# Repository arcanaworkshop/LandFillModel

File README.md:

# README Landfill Model Guide

Create by George Spearing for Arcana Workshop
March 2020

## Purpose

The lanfill model is run by an Arduino Nano with a breakout board to control audio track files. The audio track files live on the microSD card in the breakout board. Formmating for files are shown below.

## Audio Track Naming

The audio tracks are labeled using the scheme "TRACK000.wav" where "000" is the track identifier. These track numbers correspond to the buttons which light up specific sections.

## Track Numbering

- "000" Electric Power Plant
- "001" Empty - Not Used
- "002" Ground Water
- "003" Ground Liner
- "004" Leache Runoff
- "005" Gas Collection
- "006" Garbage Layer
- "007" Ground (Surface Layer)

## Track Formatting

The Arduino uses the TMRpcm library to play audio track from a microSD card. The full documentation for this library can be found at [https://github.com/TMRh20/TMRpcm/wiki](https://github.com/TMRh20/TMRpcm/wiki).

In summary, the tracks should be formatted as follows:

- Mono track
- 32000Hz (22050, 1600, 11025 also work)
- WAV, Unsigned 8 bit PCM

## Programming

I hope this doesn't need to be reprogrammed. There are two nano boards. 1 is the master and mainly controls all the leds. This is also the master to control the slave arduino file playing. The salve nano is a dedicated audio interpreter and player. This uses the micro SD card breakout. To program the slave nano, the SD car must NOT be connected. the MISO/MISI connections with the usbtiny during programming fail the upload. There is a switch on the circuit board that disables the SD card interface. Turn this off when progrmaming. DON'T FORGET TO TURN BACK ON ONCE DONE.

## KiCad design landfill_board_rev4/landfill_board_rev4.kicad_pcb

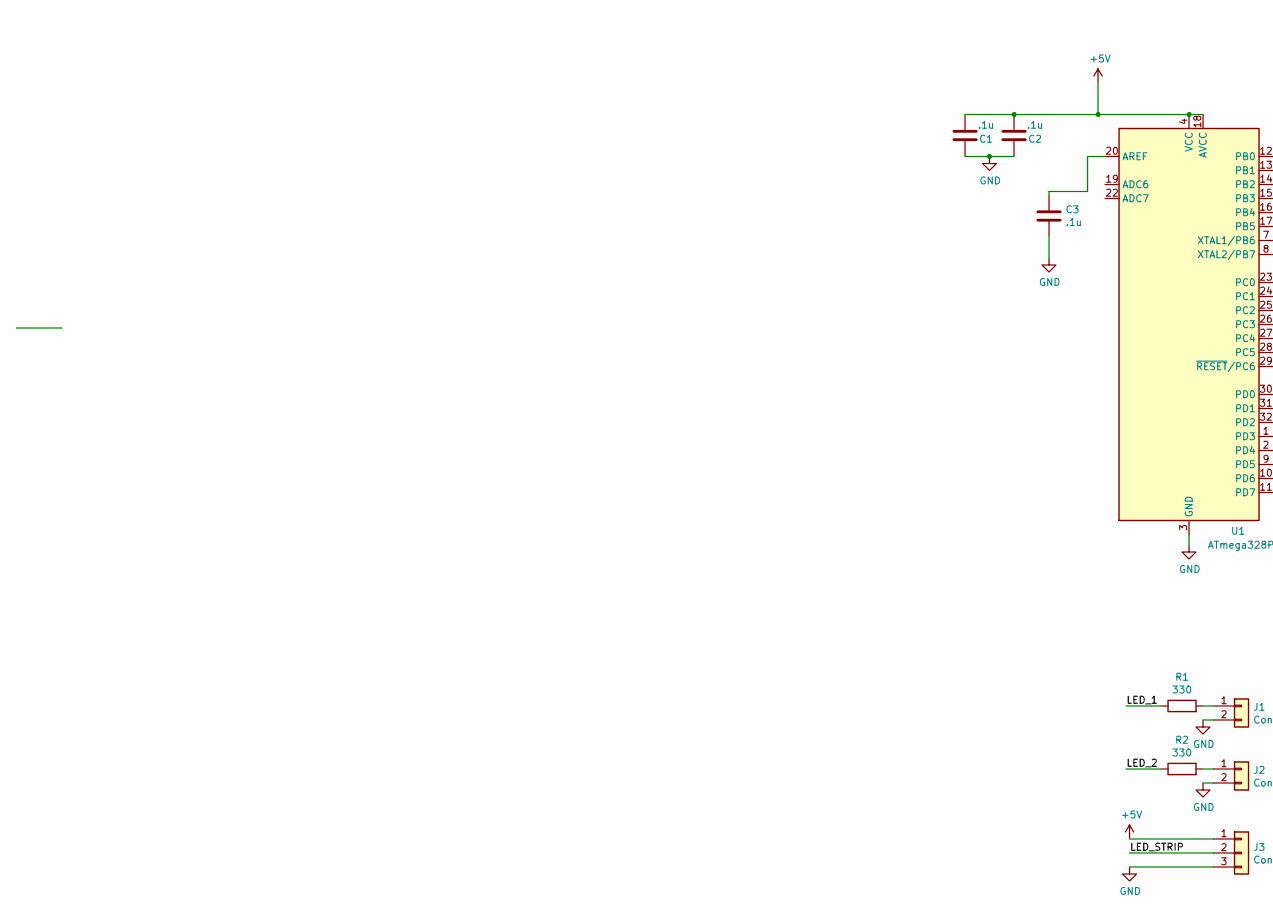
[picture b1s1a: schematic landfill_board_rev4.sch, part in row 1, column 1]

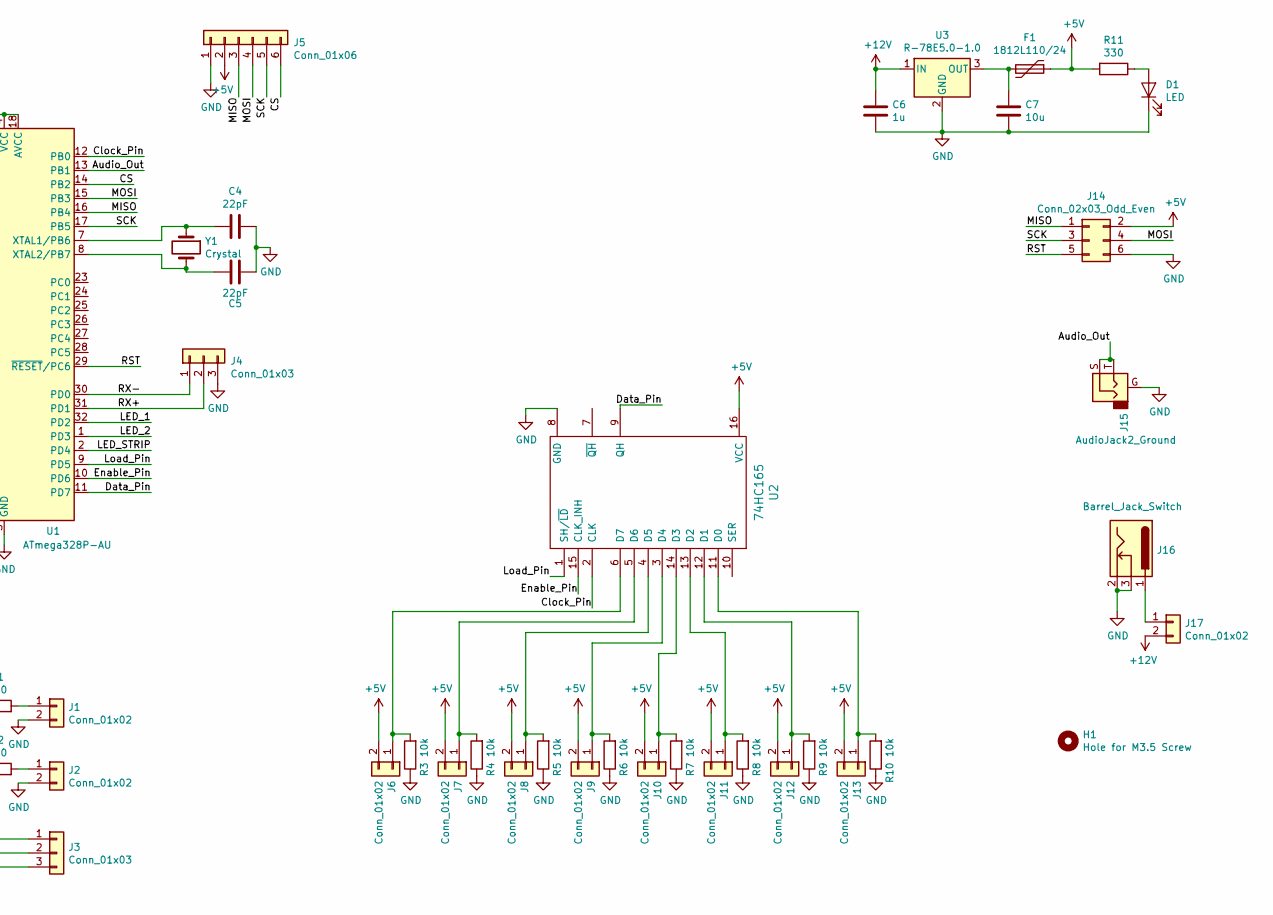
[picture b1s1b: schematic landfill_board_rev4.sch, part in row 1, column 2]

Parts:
C1, C2, C3: .1u; C_0603_1608Metric_Pad1.05x0.95mm_HandSolder
C4, C5: 22pF; C_0603_1608Metric_Pad1.05x0.95mm_HandSolder
C6: 1u; C_0603_1608Metric_Pad1.05x0.95mm_HandSolder
C7: 10u; C_0603_1608Metric_Pad1.05x0.95mm_HandSolder
D1: LED; LED_0603_1608Metric_Pad1.05x0.95mm_HandSolder
F1: 1812L110/24; Fuse_1812_4532Metric_Pad1.30x3.40mm_HandSolder
H1: Hole for M3.5 Screw; MountingHole_3.5mm
J1, J2, J6, J7, J8, J9, J10, J11, J12, J13, J17: Conn_01x02; JST_PH_B2B-PH-K_1x02_P2.00mm_Vertical
J3: Conn_01x03; JST_PH_B3B-PH-K_1x03_P2.00mm_Vertical
J4: Conn_01x03; PinSocket_1x03_P2.54mm_Vertical
J5: Conn_01x06; PinHeader_1x06_P2.54mm_Vertical
J14: Conn_02x03_Odd_Even; PinHeader_2x03_P2.54mm_Vertical
J15: AudioJack2_Ground; Jack_3.5mm_CUI_SJ-3523-SMT_Horizontal
J16: Barrel_Jack_Switch; BarrelJack_CUI_PJ-036AH-SMT_Horizontal
R1, R2, R11: 330; R_0603_1608Metric_Pad1.05x0.95mm_HandSolder
R3, R4, R5, R6, R7, R8, R9, R10: 10k; R_0603_1608Metric_Pad1.05x0.95mm_HandSolder
U1: ATmega328P-AU; TQFP-32_7x7mm_P0.8mm
U2: 74HC165; SOIC-16_3.9x9.9mm_P1.27mm
U3: R-78E5.0-1.0; Converter_DCDC_RECOM_R-78E-0.5_THT
Y1: Crystal; Crystal_HC49-U_Vertical

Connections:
+5V: C1.2, C2.2, F1.1, J3.1, J5.2, J6.2, J7.2, J8.2, J9.2, J10.2, J11.2, J12.2, J13.2, J14.2, R11.2, U1.4 (VCC), U1.6 (VCC), U1.18 (AVCC), U2.16 (VCC)
+12V: C6.1, J17.2, U3.1 (IN)
/Audio_Out: J15.S, J15.T, U1.13 (PB1)
/CS: J5.6, U1.14 (PB2)
/Clock_Pin: U1.12 (PB0), U2.2 (CLK)
/Data_Pin: U1.11 (PD7), U2.9 (QH)
/Enable_Pin: U1.10 (PD6), U2.15 (CLK_INH)
/LED_1: R1.1, U1.32 (PD2)
/LED_2: R2.1, U1.1 (PD3)
/LED_STRIP: J3.2, U1.2 (PD4)
/Load_Pin: U1.9 (PD5), U2.1 (SH/~LD)
/MISO: J5.3, J14.1, U1.16 (PB4)
/MOSI: J5.4, J14.4, U1.15 (PB3)
/RST: J14.5, U1.29 (~RESET~/PC6)
/RX+: J4.2, U1.31 (PD1)
/RX-: J4.1, U1.30 (PD0)
/SCK: J5.5, J14.3, U1.17 (PB5)
GND: C1.1, C2.1, C3.2, C4.1, C5.1, C6.2, C7.2, D1.1 (K), J1.2, J2.2, J3.3, J4.3, J5.1, J14.6, J15.G, J16.2, J16.3, R3.1, R4.1, R5.1, R6.1, R7.1, R8.1, R9.1, R10.1, U1.3 (GND), U1.5 (GND), U1.21 (GND), U2.8 (GND), U3.2 (GND)
unnamed: C3.1, U1.20 (AREF)
unnamed: C4.2, U1.7 (XTAL1/PB6), Y1.1
unnamed: C5.2, U1.8 (XTAL2/PB7), Y1.2
unnamed: C7.1, F1.2, U3.3 (OUT)
unnamed: D1.2 (A), R11.1
unnamed: J1.1, R1.2
unnamed: J2.1, R2.2
unnamed: J6.1, R3.2, U2.6 (D7)
unnamed: J7.1, R4.2, U2.5 (D6)
unnamed: J8.1, R5.2, U2.4 (D5)
unnamed: J9.1, R6.2, U2.3 (D4)
unnamed: J10.1, R7.2, U2.14 (D3)
unnamed: J11.1, R8.2, U2.13 (D2)
unnamed: J12.1, R9.2, U2.12 (D1)
unnamed: J13.1, R10.2, U2.11 (D0)
unnamed: J16.1, J17.1

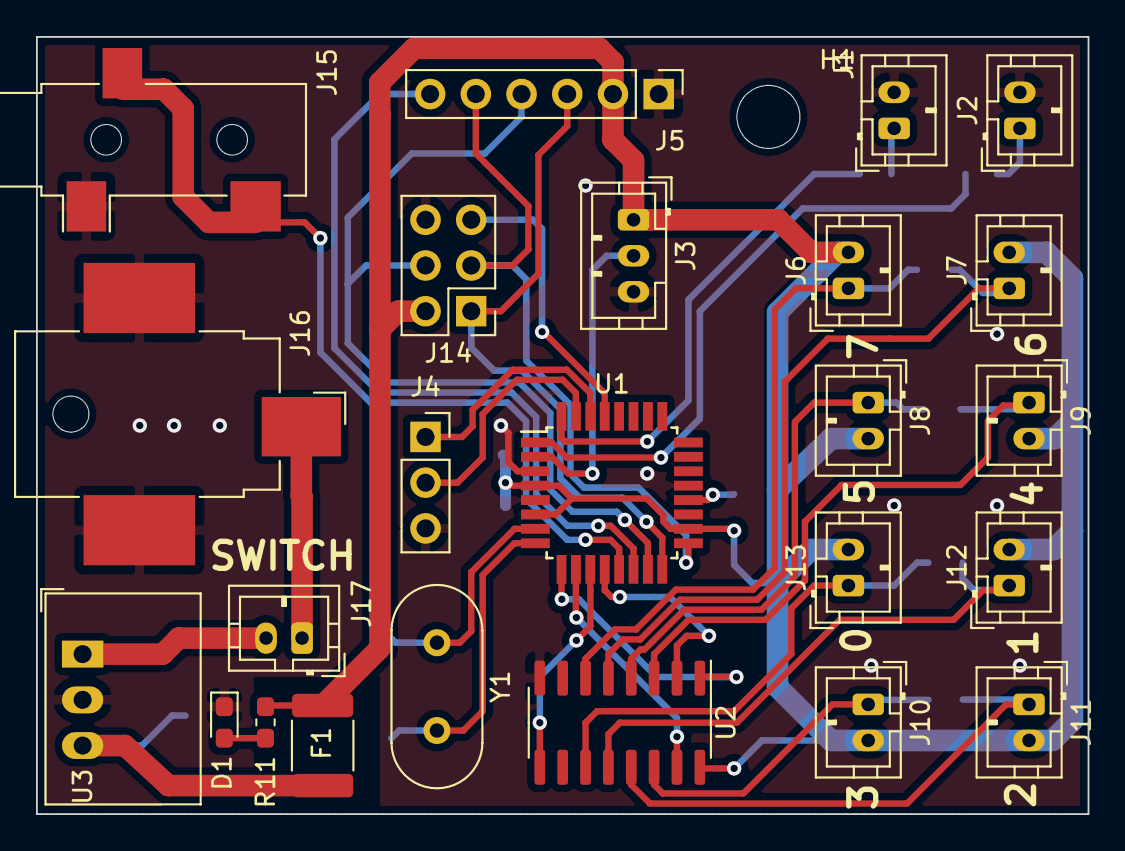
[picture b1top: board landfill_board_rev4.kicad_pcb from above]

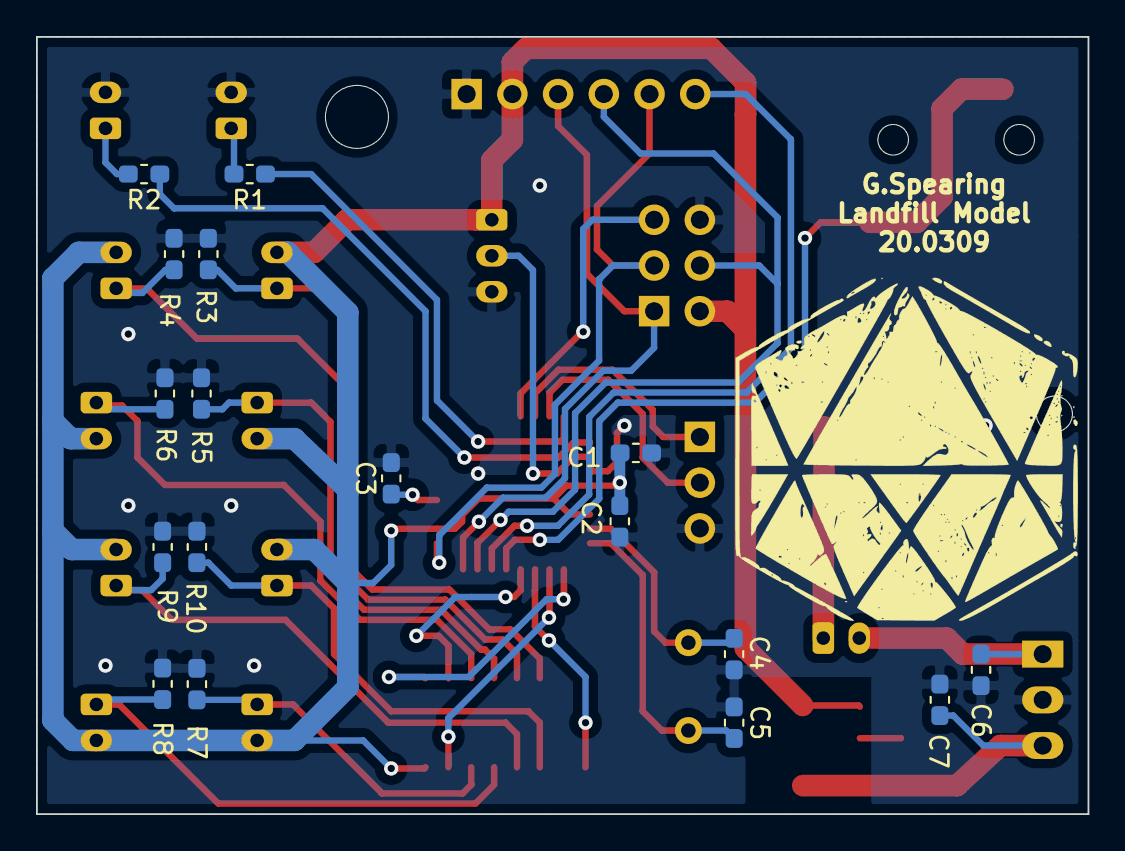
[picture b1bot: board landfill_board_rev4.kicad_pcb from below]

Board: 2 copper layers, 58.4 x 43.2 mm, 42 parts (17 on the bottom side), 34 nets.

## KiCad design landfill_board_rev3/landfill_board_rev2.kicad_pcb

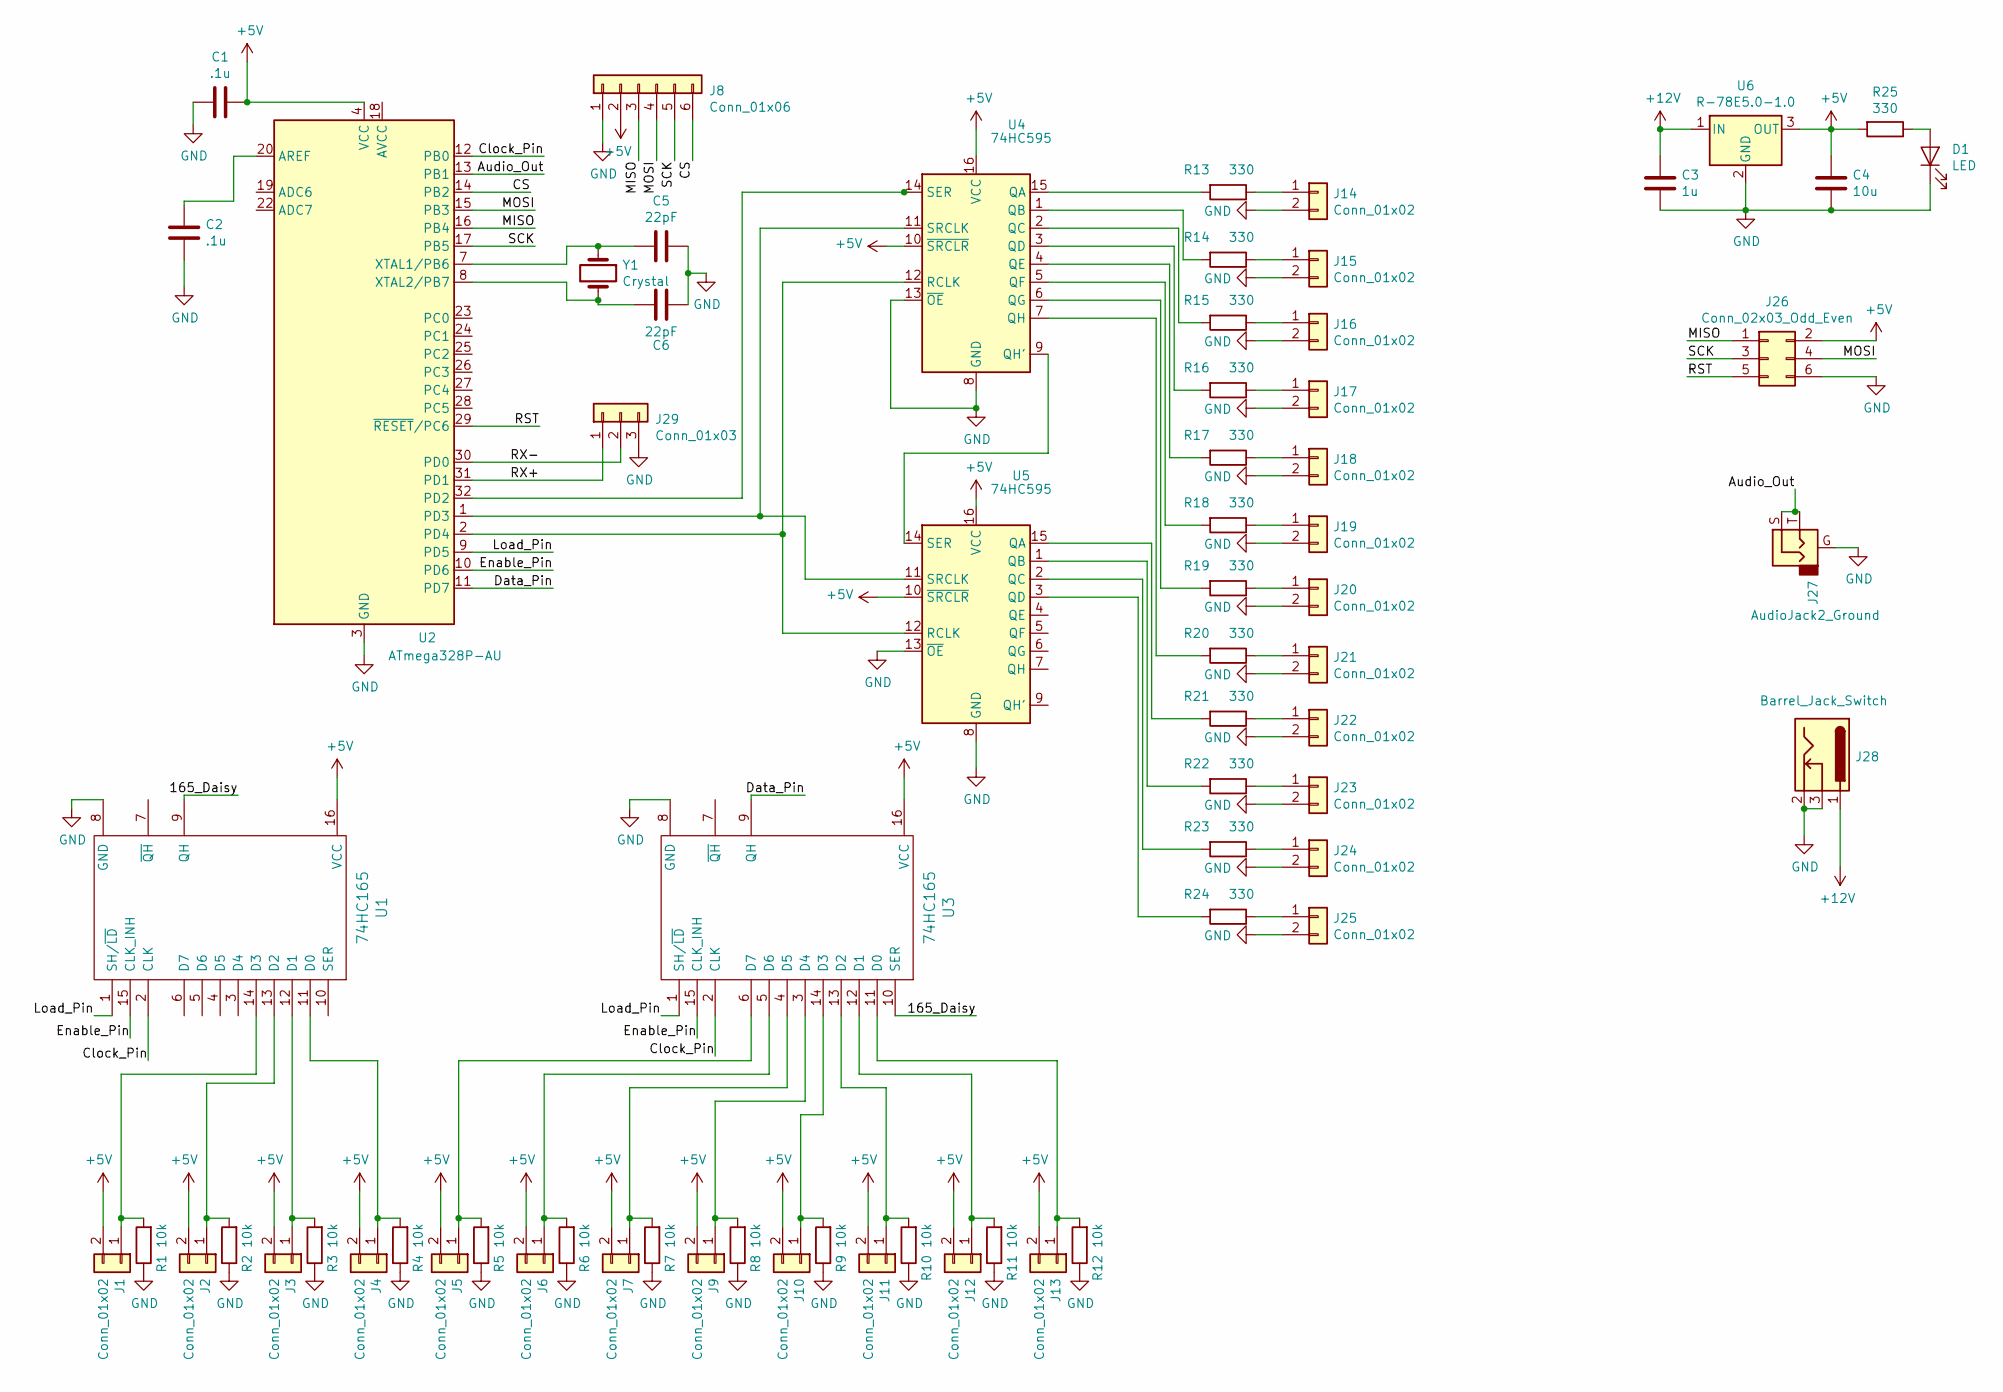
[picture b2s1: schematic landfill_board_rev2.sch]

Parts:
C1, C2: .1u; C_0603_1608Metric_Pad1.05x0.95mm_HandSolder
C3: 1u; C_0603_1608Metric_Pad1.05x0.95mm_HandSolder
C4: 10u; C_0603_1608Metric_Pad1.05x0.95mm_HandSolder
C5, C6: 22pF; C_0603_1608Metric_Pad1.05x0.95mm_HandSolder
D1: LED; LED_0603_1608Metric_Pad1.05x0.95mm_HandSolder
J1, J2, J3, J4, J5, J6, J7, J9, J10, J11, J12, J13, J14, J15, J16, J17, J18, J19, J20, J21, J22, J23, J24, J25: Conn_01x02; PinHeader_1x02_P2.00mm_Vertical
J8: Conn_01x06; PinHeader_1x06_P2.54mm_Vertical
J26: Conn_02x03_Odd_Even; PinHeader_2x03_P2.54mm_Vertical
J27: AudioJack2_Ground; Jack_3.5mm_CUI_SJ-3523-SMT_Horizontal
J28: Barrel_Jack_Switch; BarrelJack_CUI_PJ-036AH-SMT_Horizontal
J29: Conn_01x03; PinSocket_1x03_P2.54mm_Vertical
R1, R2, R3, R4, R5, R6, R7, R8, R9, R10, R11, R12: 10k; R_0603_1608Metric_Pad1.05x0.95mm_HandSolder
R13, R14, R15, R16, R17, R18, R19, R20, R21, R22, R23, R24, R25: 330; R_0603_1608Metric_Pad1.05x0.95mm_HandSolder
U1, U3: 74HC165; SOIC-16_3.9x9.9mm_P1.27mm
U2: ATmega328P-AU; TQFP-32_7x7mm_P0.8mm
U4, U5: 74HC595; SSOP-16_4.4x5.2mm_P0.65mm
U6: R-78E5.0-1.0; Converter_DCDC_RECOM_R-78E-0.5_THT
Y1: Crystal; Crystal_HC49-U_Vertical

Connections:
+5V: C1.1, C4.1, J1.2, J2.2, J3.2, J4.2, J5.2, J6.2, J7.2, J8.2, J9.2, J10.2, J11.2, J12.2, J13.2, J26.2, R25.2, U1.16 (VCC), U2.4 (VCC), U2.6 (VCC), U3.16 (VCC), U4.10 (~SRCLR), U4.16 (VCC), U5.10 (~SRCLR), U5.16 (VCC), U6.3 (OUT)
+12V: C3.1, J28.1, U6.1 (IN)
/165_Daisy: U1.9 (QH), U3.10 (SER)
/Audio_Out: J27.S, J27.T, U2.13 (PB1)
/CS: J8.6, U2.14 (PB2)
/Clock_Pin: U1.2 (CLK), U2.12 (PB0), U3.2 (CLK)
/Data_Pin: U2.11 (PD7), U3.9 (QH)
/Enable_Pin: U1.15 (CLK_INH), U2.10 (PD6), U3.15 (CLK_INH)
/Load_Pin: U1.1 (SH/~LD), U2.9 (PD5), U3.1 (SH/~LD)
/MISO: J8.3, J26.1, U2.16 (PB4)
/MOSI: J8.4, J26.4, U2.15 (PB3)
/RST: J26.5, U2.29 (~RESET~/PC6)
/RX+: J29.1, U2.31 (PD1)
/RX-: J29.2, U2.30 (PD0)
/SCK: J8.5, J26.3, U2.17 (PB5)
GND: C1.2, C2.2, C3.2, C4.2, C5.1, C6.1, D1.1 (K), J8.1, J14.2, J15.2, J16.2, J17.2, J18.2, J19.2, J20.2, J21.2, J22.2, J23.2, J24.2, J25.2, J26.6, J27.G, J28.2, J28.3, J29.3, R1.1, R2.1, R3.1, R4.1, R5.1, R6.1, R7.1, R8.1, R9.1, R10.1, R11.1, R12.1, U1.8 (GND), U2.3 (GND), U2.5 (GND), U2.21 (GND), U3.8 (GND), U4.8 (GND), U4.13 (~OE), U5.8 (GND), U5.13 (~OE), U6.2 (GND)
unnamed: C2.1, U2.20 (AREF)
unnamed: C5.2, U2.7 (XTAL1/PB6), Y1.1
unnamed: C6.2, U2.8 (XTAL2/PB7), Y1.2
unnamed: D1.2 (A), R25.1
unnamed: J1.1, R1.2, U1.14 (D3)
unnamed: J2.1, R2.2, U1.13 (D2)
unnamed: J3.1, R3.2, U1.12 (D1)
unnamed: J4.1, R4.2, U1.11 (D0)
unnamed: J5.1, R5.2, U3.6 (D7)
unnamed: J6.1, R6.2, U3.5 (D6)
unnamed: J7.1, R7.2, U3.4 (D5)
unnamed: J9.1, R8.2, U3.3 (D4)
unnamed: J10.1, R9.2, U3.14 (D3)
unnamed: J11.1, R10.2, U3.13 (D2)
unnamed: J12.1, R11.2, U3.12 (D1)
unnamed: J13.1, R12.2, U3.11 (D0)
unnamed: J14.1, R13.1
unnamed: J15.1, R14.1
unnamed: J16.1, R15.1
unnamed: J17.1, R16.1
unnamed: J18.1, R17.1
unnamed: J19.1, R18.1
unnamed: J20.1, R19.1
unnamed: J21.1, R20.1
unnamed: J22.1, R21.1
unnamed: J23.1, R22.1
unnamed: J24.1, R23.1
unnamed: J25.1, R24.1
unnamed: R13.2, U4.15 (QA)
unnamed: R14.2, U4.1 (QB)
unnamed: R15.2, U4.2 (QC)
unnamed: R16.2, U4.3 (QD)
unnamed: R17.2, U4.4 (QE)
unnamed: R18.2, U4.5 (QF)
unnamed: R19.2, U4.6 (QG)
unnamed: R20.2, U4.7 (QH)
unnamed: R21.2, U5.15 (QA)
unnamed: R22.2, U5.1 (QB)
unnamed: R23.2, U5.2 (QC)
unnamed: R24.2, U5.3 (QD)
unnamed: U2.1 (PD3), U4.11 (SRCLK), U5.11 (SRCLK)
unnamed: U2.2 (PD4), U4.12 (RCLK), U5.12 (RCLK)
unnamed: U2.32 (PD2), U4.14 (SER)
unnamed: U4.9 (QH'), U5.14 (SER)

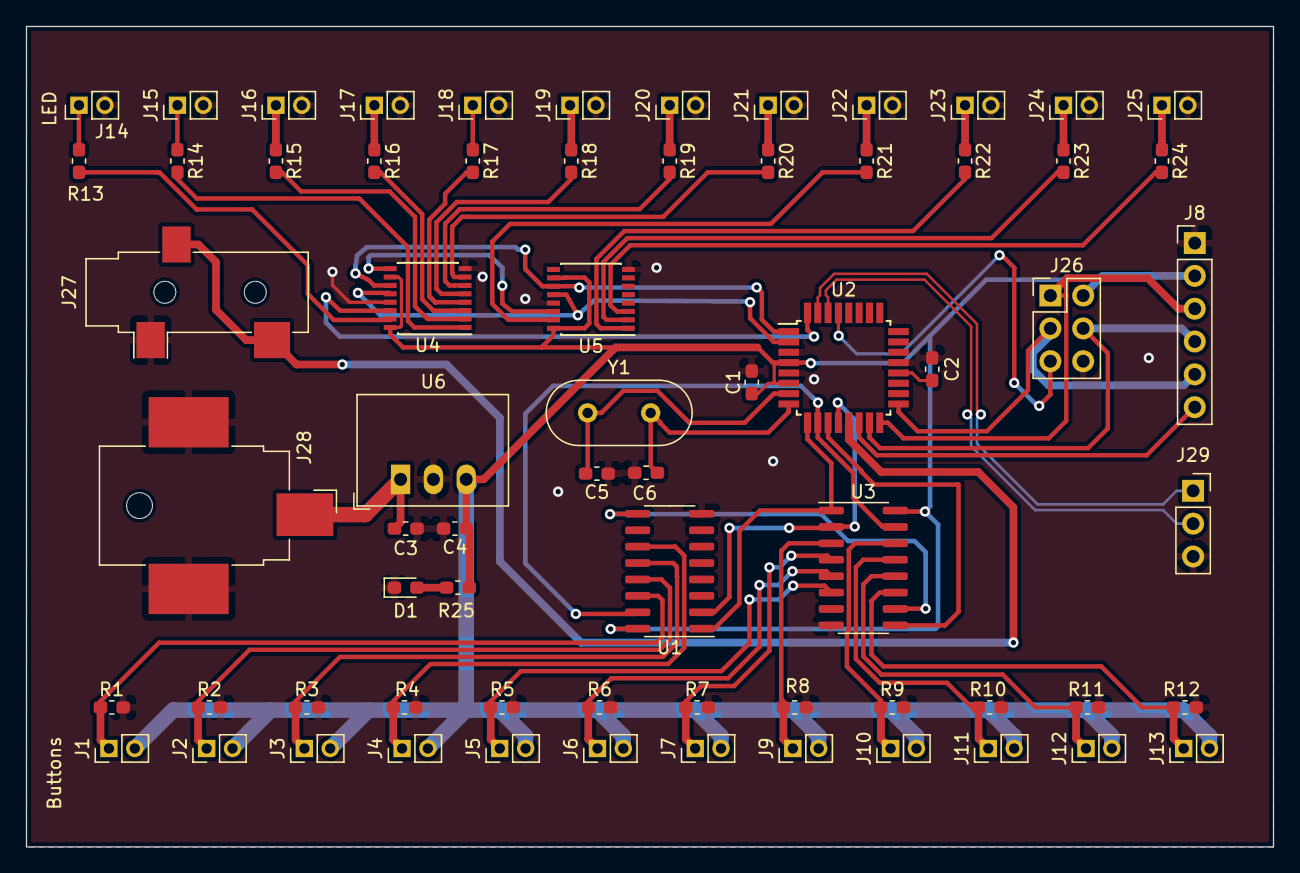
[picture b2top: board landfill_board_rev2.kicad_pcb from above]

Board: 2 copper layers, 96.5 x 63.5 mm, 68 parts (0 on the bottom side), 60 nets.

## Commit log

2021-03-28 initial commit code revision 0
2021-03-28 redesign board and code
2021-03-28 cleanup functionality
2021-03-28 add sound functionality
2021-04-08 add user guide
